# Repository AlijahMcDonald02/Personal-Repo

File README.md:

# Personal-Repo

This is your personal repository Alijah, use it for personal files you would like to store of GitHub

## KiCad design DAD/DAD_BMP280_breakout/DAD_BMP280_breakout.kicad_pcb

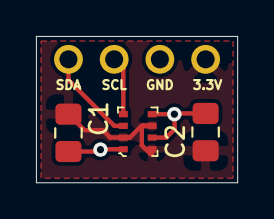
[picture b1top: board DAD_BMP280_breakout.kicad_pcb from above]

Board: 2 copper layers, 11.2 x 8.1 mm, 4 parts (0 on the bottom side), 4 nets.

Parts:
C1, C2: 100nF; C_0805_2012Metric_Pad1.18x1.45mm_HandSolder
J1: Conn_01x04_Male; Baro_4pin_connector
U1: BMP280; LGA-8_2x2.5mm_BMP280

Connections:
+3V3: C1.1, C2.1, J1.1, U1.2, U1.6, U1.8
/SCL: J1.3, U1.4
/SDA: J1.4, U1.3
GND: C1.2, C2.2, J1.2, U1.1, U1.5, U1.7

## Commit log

2020-12-27 Create DAD Requirements
2021-01-05 Initial File Push
2021-01-05 chek
2021-01-05 test
